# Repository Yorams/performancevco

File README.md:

# Performance VCO
Eurorack version of LMNC Performance VCO based on the AS3340 VCO IC

Link to original project: https://www.lookmumnocomputer.com/projects#/1222-performance-vco

Included is also the BOM with Farnell order codes and the links from the original project.

If you are intrested in ordering some PCB's for a small price i can help you with that. Send me an email: yscheer@gmail.com

You can get the arduino firmware for the tuner here: https://github.com/josbouten/Tune-O-Matic

# Some Images

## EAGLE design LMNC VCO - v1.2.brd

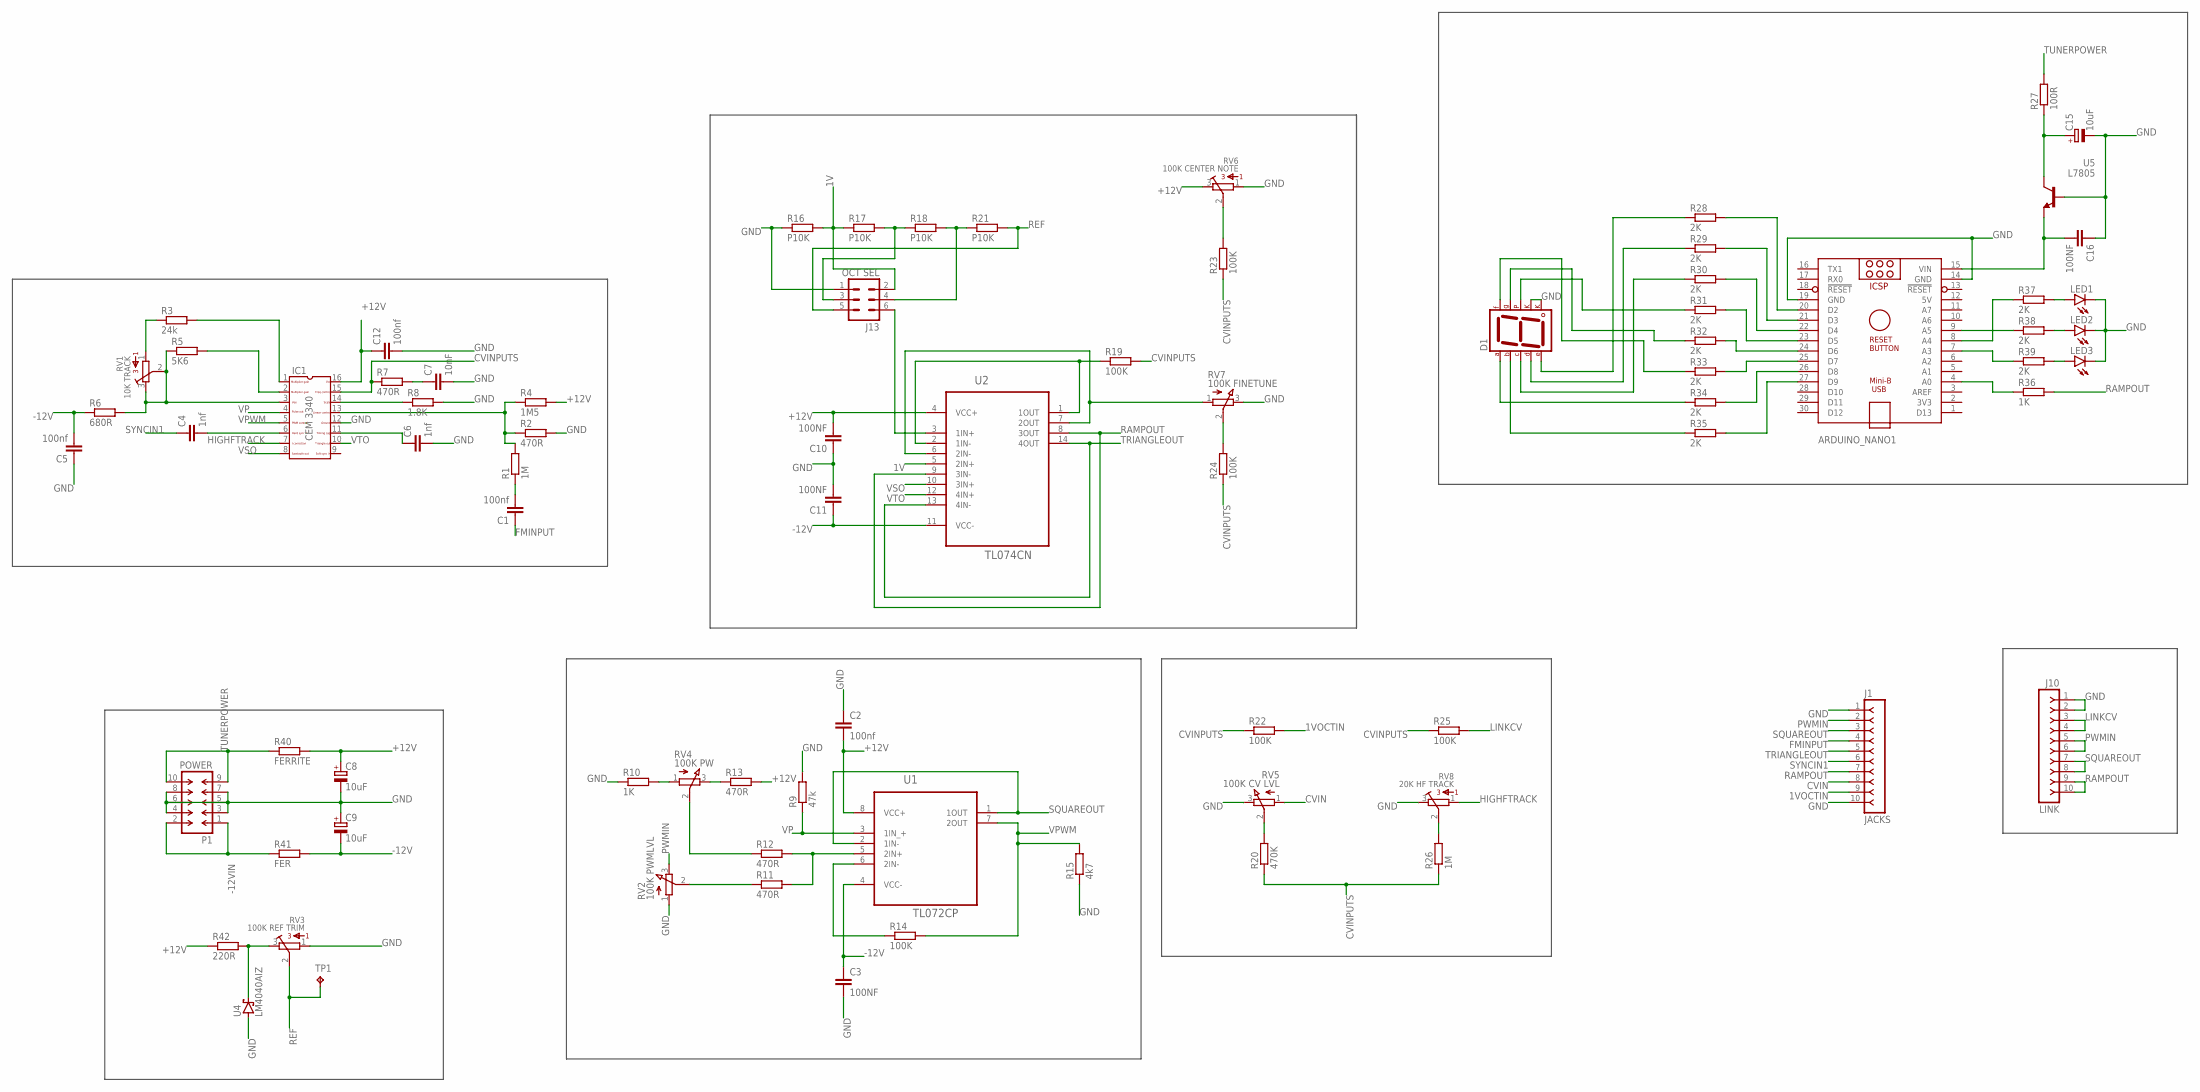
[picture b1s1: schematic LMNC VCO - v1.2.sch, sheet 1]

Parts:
ARDUINO_NANO1: ARDUINO_NANO
C1, C2, C5, C12: 100nf; C2.5-3
C3, C10, C11, C16: 100NF; C2.5-3
C4, C6: 1nf; C2.5-3
C7: 10nF; C2.5-3
C8, C9, C15: 10uF; E2,5-5
D1: 7SEG-CK; 7SEG-13
IC1: CEM3340; DIL16
J1: JACKS; SIP-100-10-32Y
J10: LINK; SIP-100-10-32Y
J13: OCT SEL; MA03-2
LED1, LED2, LED3: LED3MM
P1: POWER; DIL-100-2X05
R1, R26: 1M; 0207/10
R2, R7, R11, R12, R13: 470R; 0207/10
R3: 24k; 0207/10
R4: 1M5; 0207/10
R5: 5K6; 0207/10
R6: 680R; 0207/10
R8: 1.8K; 0207/10
R9: 47k; 0207/10
R10, R36: 1K; 0207/10
R14, R19, R22, R23, R24, R25: 100K; 0207/10
R15: 4k7; 0207/10
R16, R17, R18, R21: P10K; 0207/10
R20: 470K; 0207/10
R27: 100R; 0207/10
R28, R29, R30, R31, R32, R33, R34, R35, R37, R38, R39: 2K; 0207/10
R40: FERRITE; 0207/10
R41: FER; 0207/10
R42: 220R; 0207/10
RV1: 10K TRACK; 3386W
RV2: 100K PWMLVL; EVUF
RV3: 100K REF TRIM; 3386W
RV4: 100K PW; EVUF
RV5: 100K CV LVL; EVUF
RV6: 100K CENTER NOTE; 3386W
RV7: 100K FINETUNE; EVUF
RV8: 20K HF TRACK; 3386W
TP1: 4v; B2,54
U1: TL072CP; DIP254P762X508-8
U2: TL074CN; DIP254P762X508-14
U4: LM4040AIZ; SOT54A
U5: L7805; TO220BV

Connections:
1V: J13.2, R16.2, R17.1, U2.5 (2IN+)
1VOCTIN: J1.9, R22.2
5V: ARDUINO_NANO1.12 (5V)
+12V: C2.2, C8.+, C10.2, C12.1, IC1.16, R4.2, R13.2, R40.2, R42.1, RV6.3, U1.8 (VCC+), U2.4 (VCC+)
-12V: C3.1, C5.2, C9.-, C11.1, R6.1, R41.2, U1.4 (VCC-), U2.11 (VCC-)
-12VIN: P1.1, P1.2, R41.1
CVIN: J1.8, RV5.1 (A)
CVINPUTS: IC1.15, R7.1, R19.2, R20.1, R22.1, R23.1, R24.1, R25.1, R26.1
FMINPUT: C1.1, J1.4
GND: ARDUINO_NANO1.14 (GND), ARDUINO_NANO1.19 (GND), C2.1, C3.2, C5.1, C6.2, C7.2, C8.-, C9.+, C10.1, C11.2, C12.2, C15.-, C16.1, D1.3 (CK1), D1.8 (CK2), IC1.12, J1.1, J1.10, J10.1, J10.2, J13.1, LED1.K (C), LED2.K (C), LED3.K (C), P1.3, P1.4, P1.5, P1.6, P1.7, P1.8, R2.2, R8.2, R9.2, R10.1, R15.1, R16.1, RV2.1 (A), RV3.1, RV5.3 (E), RV6.1, RV7.3 (E), RV8.3, U4.A1 (A), U5.1 (B)
HIGHFTRACK: IC1.7, RV8.1
LINKCV: J10.3, J10.4, R25.2
unnamed: IC1.2, R5.2
unnamed: IC1.1, R3.2
unnamed: IC1.3, R5.1, R6.2, RV1.2, RV1.3
unnamed: R3.1, RV1.1
unnamed: C7.1, R7.2
unnamed: C1.2, R1.1
unnamed: C4.2, IC1.6
unnamed: C6.1, IC1.11
unnamed: R14.1, U1.6 (2IN-)
unnamed: R11.2, R12.2, U1.5 (2IN+)
unnamed: IC1.14, R8.1
unnamed: IC1.13, R1.2, R2.1, R4.1
unnamed: R12.1, RV4.2 (S)
unnamed: R11.1, RV2.2 (S)
unnamed: R10.2, RV4.1 (A)
unnamed: R13.1, RV4.3 (E)
unnamed: RV7.1 (A), U2.6 (2IN-), U2.7 (2OUT)
unnamed: J13.6, U2.3 (1IN+)
unnamed: C15.+, R27.1, U5.2 (C)
unnamed: J13.3, R17.2, R18.1
unnamed: J13.4, R18.2, R21.1
unnamed: R24.2, RV7.2 (S)
unnamed: R19.1, U2.1 (1OUT), U2.2 (1IN-)
unnamed: R23.2, RV6.2
unnamed: ARDUINO_NANO1.24 (D6), R32.2
unnamed: R20.2, RV5.2 (S)
unnamed: R26.2, RV8.2
unnamed: R42.2, RV3.3, U4.A2 (C)
unnamed: ARDUINO_NANO1.25 (D7), R33.2
unnamed: ARDUINO_NANO1.26 (D8), R34.2
unnamed: ARDUINO_NANO1.27 (D9), R35.2
unnamed: ARDUINO_NANO1.23 (D5), R31.2
unnamed: ARDUINO_NANO1.22 (D4), R30.2
unnamed: ARDUINO_NANO1.21 (D3), R29.2
unnamed: ARDUINO_NANO1.20 (D2), R28.2
unnamed: ARDUINO_NANO1.9 (A5), R38.1
unnamed: ARDUINO_NANO1.7 (A3), R39.1
unnamed: ARDUINO_NANO1.8 (A4), R37.1
unnamed: LED1.A, R37.2
unnamed: LED2.A, R38.2
unnamed: LED3.A, R39.2
unnamed: ARDUINO_NANO1.4 (A0), R36.1
unnamed: ARDUINO_NANO1.15 (VIN), C16.2, U5.3 (E)
unnamed: D1.6 (B), R35.1
unnamed: D1.7 (A), R34.1
unnamed: D1.4 (C), R30.1
unnamed: D1.2 (D), R29.1
unnamed: D1.1 (E), R28.1
unnamed: D1.9 (F), R33.1
unnamed: D1.10 (G), R32.1
unnamed: D1.5 (DP), R31.1
PWMIN: J1.2, J10.5, J10.6, RV2.3 (E)
RAMPOUT: J1.7, J10.9, J10.10, R36.2, U2.8 (3OUT), U2.9 (3IN-)
REF: J13.5, R21.2, RV3.2, TP1.TP
SQUAREOUT: J1.3, J10.7, J10.8, U1.1 (1OUT), U1.2 (1IN-)
SYNCIN1: C4.1, J1.6
TRIANGLEOUT: J1.5, U2.13 (4IN-), U2.14 (4OUT)
TUNERPOWER: P1.9, P1.10, R27.2, R40.1
VP: IC1.4, R9.1, U1.3 (1IN_+)
VPWM: IC1.5, R14.2, R15.2, U1.7 (2OUT)
VSO: IC1.8, U2.10 (3IN+)
VTO: IC1.10, U2.12 (4IN+)

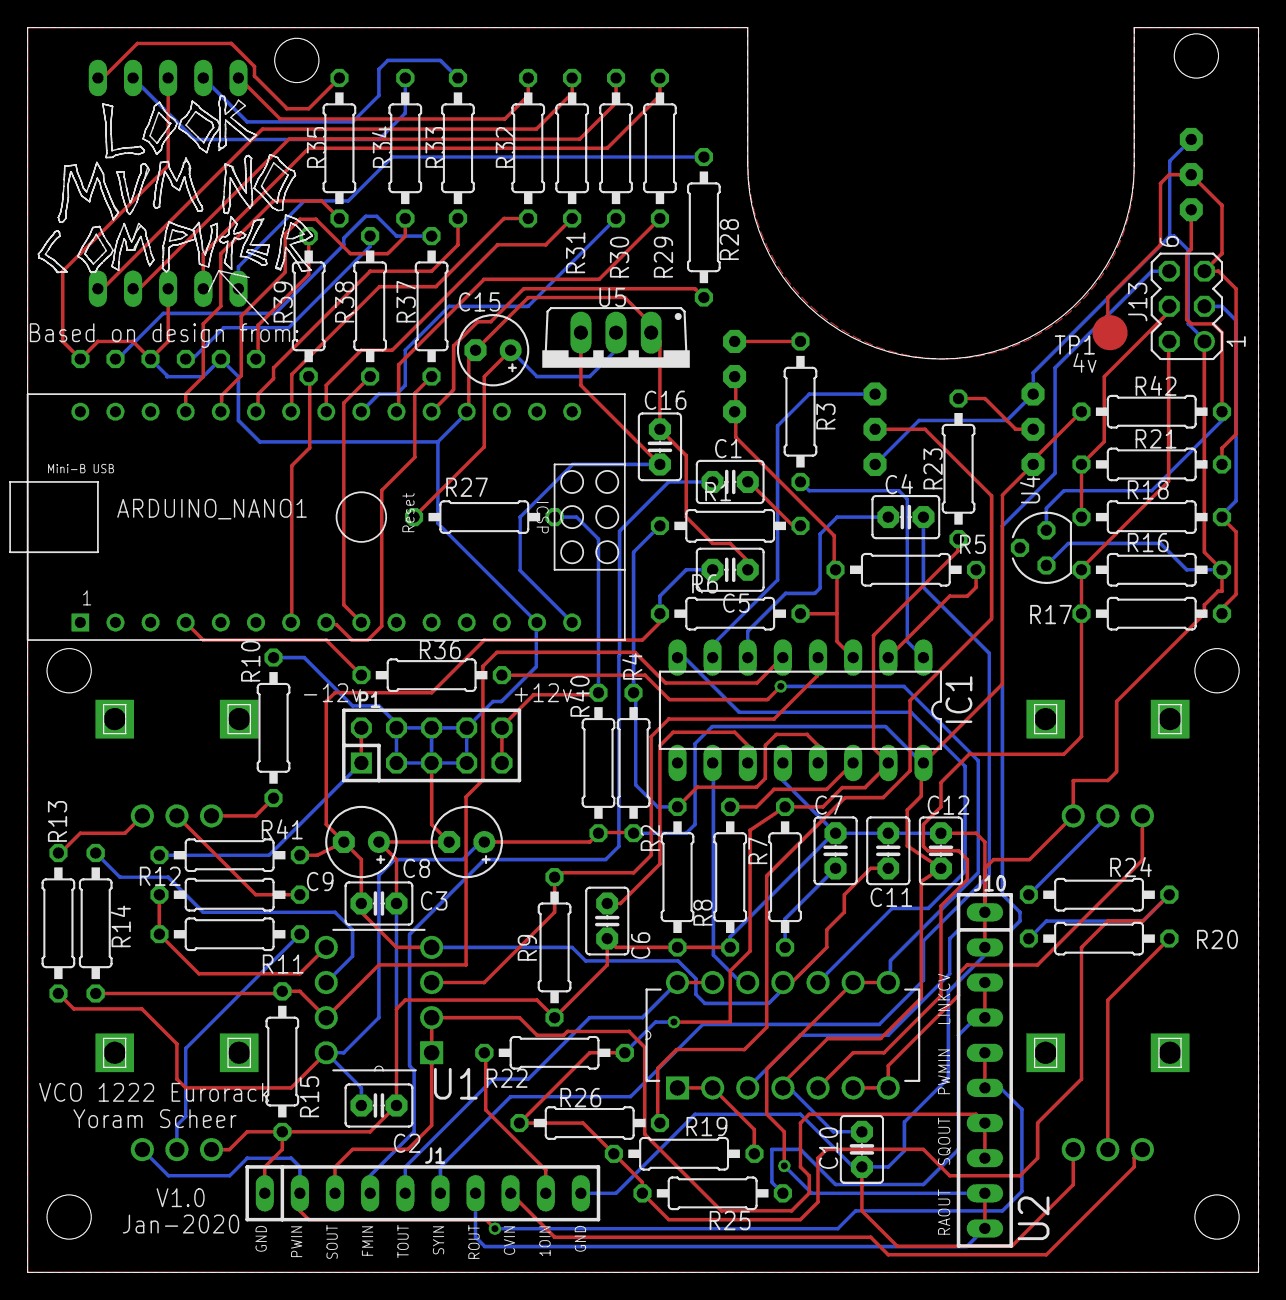
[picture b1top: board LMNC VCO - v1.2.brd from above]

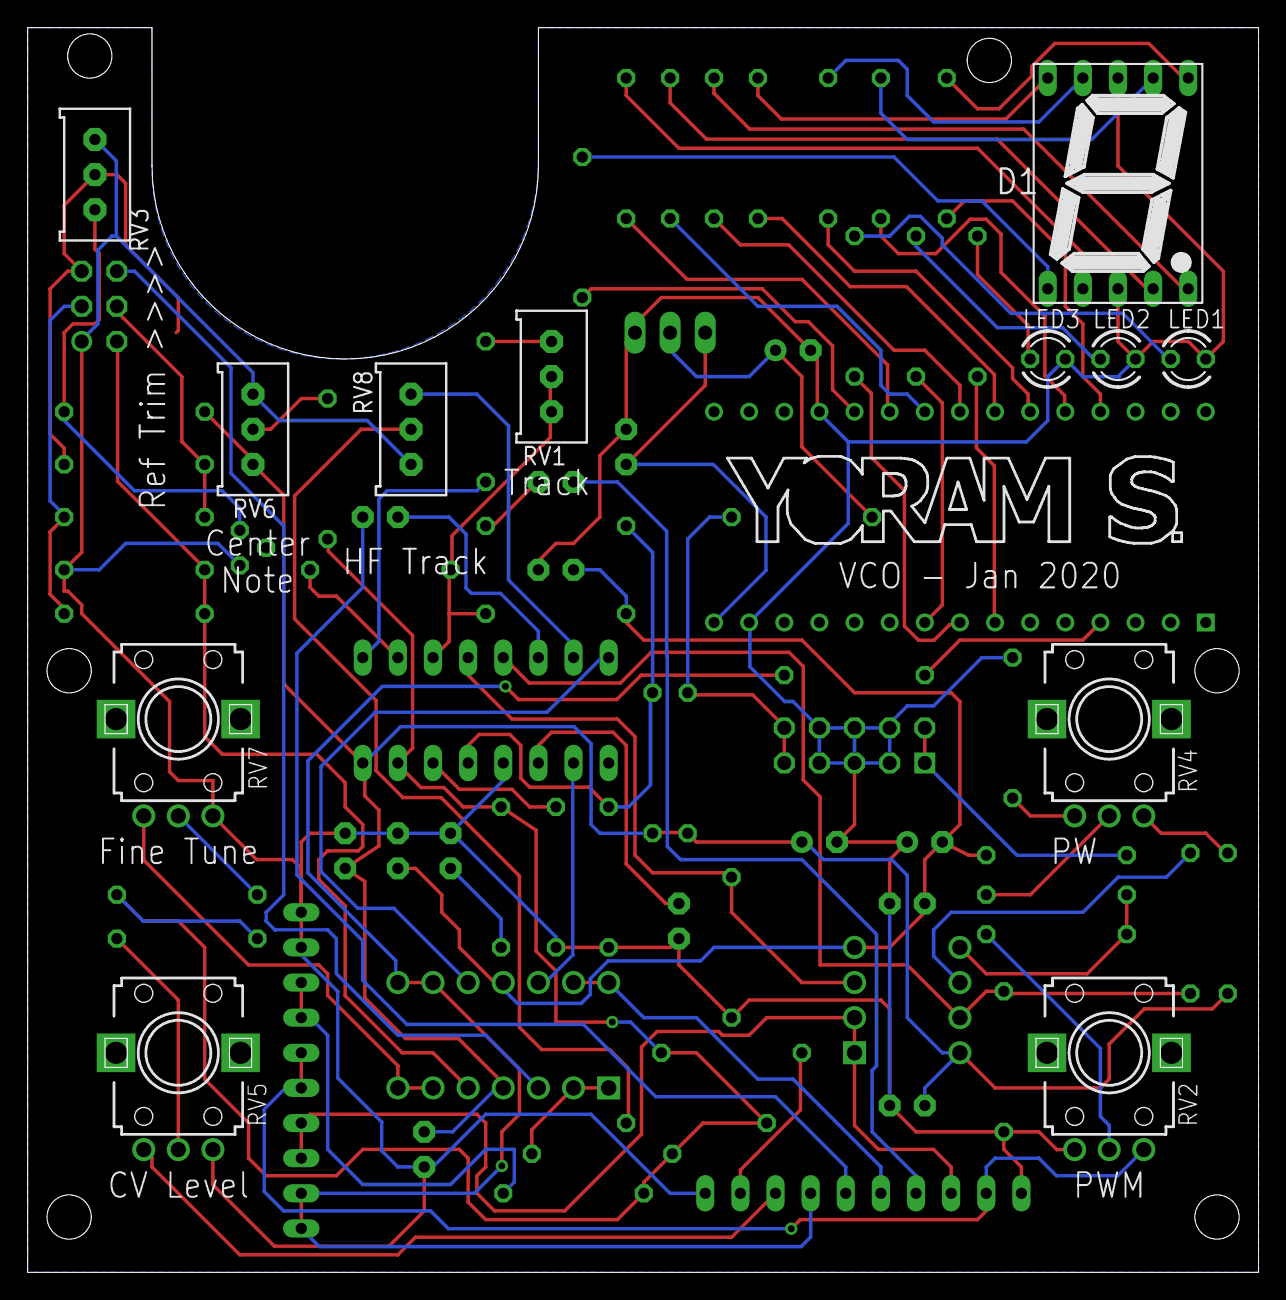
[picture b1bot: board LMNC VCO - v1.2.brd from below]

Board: 2 copper layers, 89.0 x 90.0 mm, 79 parts (12 on the bottom side), 73 nets.

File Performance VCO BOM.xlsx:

Designator | Description | Amount | Value | Farnell code |  | Alternative supplier
C4,C6 | Ceramic Capacitor | 2 | 1nf | 9411828 |  | https://www.rapidonline.com/suntan-ts15001h102ksbpa0r-1nf-10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
C7 | Ceramic Capacitor | 1 | 10nf | 1827843 |  | https://www.rapidonline.com/suntan-ts15001h102ksbpa0r-1nf-10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
C1,C2,C3,C5,C10,C11,C12,C16 | Ceramic Capacitor | 8 | 100nf | 9411887 |  | https://www.rapidonline.com/suntan-ts15001e104msbfbor-100nf-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
C8,C9,C15 | Electrolytic Capacitor | 3 | 10uf | 9693548 |  | https://www.rapidonline.com/forever-10uf-20-16v-85-c-7mm-mic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
D1,D2,D3 | 3mm LED’s 2 red 1 green, or whatever its up to you! | 3 | LED | 1142517 | 1142502 | https://www.rapidonline.com/kingbright-l-424hdt-3mm-2-25v-re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
DS1 | display! SC56-11EWA | 1 | SC56-11EWA | 1142441 |  | https://www.rapidonline.com/kingbright-sc56-11ewa-14-2mm-hig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
R27 | Resistor (preferable metal film 0.25W) | 1 | 100R | 9341099 |  | https://www.ebay.co.uk/itm/1280pcs-Metal-Film-Resistors-Asso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
R42 | Resistor (preferable metal film 0.25W) | 1 | 220R | 9341528
R2,R7 | Resistor (preferable metal film 0.25W) | 2 | 470R | 9341943
R6 | Resistor (preferable metal film 0.25W) | 1 | 680R | 9342150
R10,R36 | Resistor (preferable metal film 0.25W) | 2 | 1K | 9341102
R8 | Resistor (preferable metal film 0.25W) | 1 | 1.8k | 9341439
R28,R29,R30,R31,R32,R33,R34,R35,R37,R38,R39 | Resistor (preferable metal film 0.25W) | 11 | 2K | 9341480
R15 | Resistor (preferable metal film 0.25W) | 1 | 4k7 | 9341951
R5 | Resistor (preferable metal film 0.25W) | 1 | 5K6 | 9342060
R3 | Resistor (preferable metal film 0.25W) | 1 | 24K | 9341609
R9 | Resistor (preferable metal film 0.25W) | 1 | 10k/47k | 9341110
R14,R19,R22,R23,R24,R25 | Resistor (preferable metal film 0.25W) | 6 | 100K | 9341129
R11,R12,R13,R20 | Resistor (preferable metal film 0.25W) | 4 | 470K | 9341978
R1,R26 | Resistor (preferable metal film 0.25W) | 2 | 1M | 9341137
R4 | Resistor (preferable metal film 0.25W) | 1 | 1M5 | 1186237
R16,R18,R21,R17 | Resistor (preferable metal film 0.25W) precision.. watch vid | 4 | 10k | 1083362 |  | https://www.rapidonline.com/arcol-mra0207-10kbta15-10k-0-1-1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
RV1 | Potentiometer_Vertical preset pot | 1 | 10k Vertical Preset Pot | 9353186 |  | https://www.rapidonline.com/suntan-tsr-3296w-103r-10k-wr3296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
RV3,RV6 | Potentiometer_Vertical preset pot | 2 | 100k Vertical Preset Pot | 9353194 |  | https://www.rapidonline.com/suntan-tsr-3296w-104r-100k-wr329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
RV8 | Potentiometer_Vertical preset pot | 1 | 20k Vertical Preset Pot | 9353240 |  | https://www.rapidonline.com/suntan-tsr-3296w-203r-20k-wr3296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
RV2,RV4,RV5,RV7 | Potentiometer_pcb mount style I use 6.35mm round shaft, up to you | 4 | Potentiometer B100k Linear | 1191742 |  | https://www.thonk.co.uk/shop/alpha-9mm-pots/
U1 | 14 pin IC quad opamp | 1 | TL074 | 3005126 |  | https://www.rapidonline.com/Catalogue/Search?Query=tl074&Size=20
A1 | Arduino_Nano , linked is a real one, you can get away with a cheap one | 1 | ARDUINO NANO |  |  | https://www.rapidonline.com/arduino-nano-a000005-board-v3-73-4448
U2 | 8 pin IC dual opamp | 1 | TL072 | 3117788 |  | https://www.rapidonline.com/Catalogue/Search?Query=tl072&Size=20
U3 | 16 pin IC VCO chip read more on my site page on this matter | 1 | AS3340/CEM3340 |  |  | https://www.thonk.co.uk/shop/curtis-cem3340-ic-vco-chip/
U5 | TO-220 package 5v voltage regulator | 1 | L7805 | 9756078 |  | https://www.rapidonline.com/st-l7805cv-5v-1a-voltage-regulat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
U4 | TO-92_Inline_Wide precision voltage regulator | 1 | LM4040AIZ 4.1 | 3124413 |  | https://www.ebay.co.uk/itm/Texas-Instruments-LM4040AIZ-4-1-N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
R40,R41 | Ferrite cores, if you aint fussy like me just use some wire! | 2 | FERRITE | 9526820 |  | https://www.rapidonline.com/murata-bl01rn1-a62-axial-ferrite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
J1 | Multicomp_MC9A12-1034_2x05_P2.54mm_Vertical | 1 | POWER INPUT | 2215304 |  | https://www.rapidonline.com/truconnect-10-way-idc-straight-b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
J11 | PinHeader_1x12_P2.54mm_Vertical | 1 | PCB INTERCONNECT MAIN |  |  | https://www.rapidonline.com/truconnect-single-row-header-36-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
 |  |  |  |  |  | https://www.rapidonline.com/truconnect-10-way-single-row-pcb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
J12 | Multicomp_MC9A12-1034_2x05_P2.54mm_Vertical | 1 | LINK | 2215304 |  | https://www.rapidonline.com/truconnect-10-way-idc-straight-b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
J13 | Molex connector (I used pin headers for this) | 1 | Conn_01x06_Male | 9731172 |  | https://www.rapidonline.com/molex-22-27-2061-6-way-2-54mm-kk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
 |  |  |  |  |  | https://www.rapidonline.com/molex-22-27-2061-6-way-2-54mm-kk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
 |  |  |  |  |  | https://www.rapidonline.com/rvfm-ht-225d-ratchet-action-crim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
 |  |  |  |  |  | https://www.rapidonline.com/jyk-h2500-06-6-pole-crimp-housin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
Rotary switch | 12 Way Rotary Switch single pole | 1 | Octave | 1123694 |  | https://www.rapidonline.com/taiwan-alpha-sr2611f011238f5bdnl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
M3 bolt 20mm and nut | This is to add rigidity | 1
Knobs |  | 4 |  | 3052360 |  | https://www.rapidonline.com/sci-rn-117b-arrow-control-knob-2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
 |  | 1 |  | 1209771 | 1209820 | https://www.rapidonline.com/sci-rn-114b-arrow-control-knob-3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
Ic sockets |  |  |  | 2668404 |  | https://www.rapidonline.com/-tube-34-truconnect-14-pin-dil-s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
 |  |  |  | 2668408 |  | https://www.rapidonline.com/-tube-60-truconnect-8-pin-dil-so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
 |  |  |  | 2668405 |  | https://www.rapidonline.com/-tube-30-truconnect-16-pin-dil-s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
 |  |  |  | 1182595 |  | https://www.rapidonline.com/-tube-15-truconnect-32-pin-dil-s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
Power cable | A video on how to make them to come |  |  |  |  | https://www.thonk.co.uk/shop/eurorack-power-cables/

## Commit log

2020-03-22 Initial upload
2020-03-22 Readme added
2020-03-22 Added some files

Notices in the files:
parts and their libraries:
con-headers-jp: Copyright (C) 2008, Bob Starr
